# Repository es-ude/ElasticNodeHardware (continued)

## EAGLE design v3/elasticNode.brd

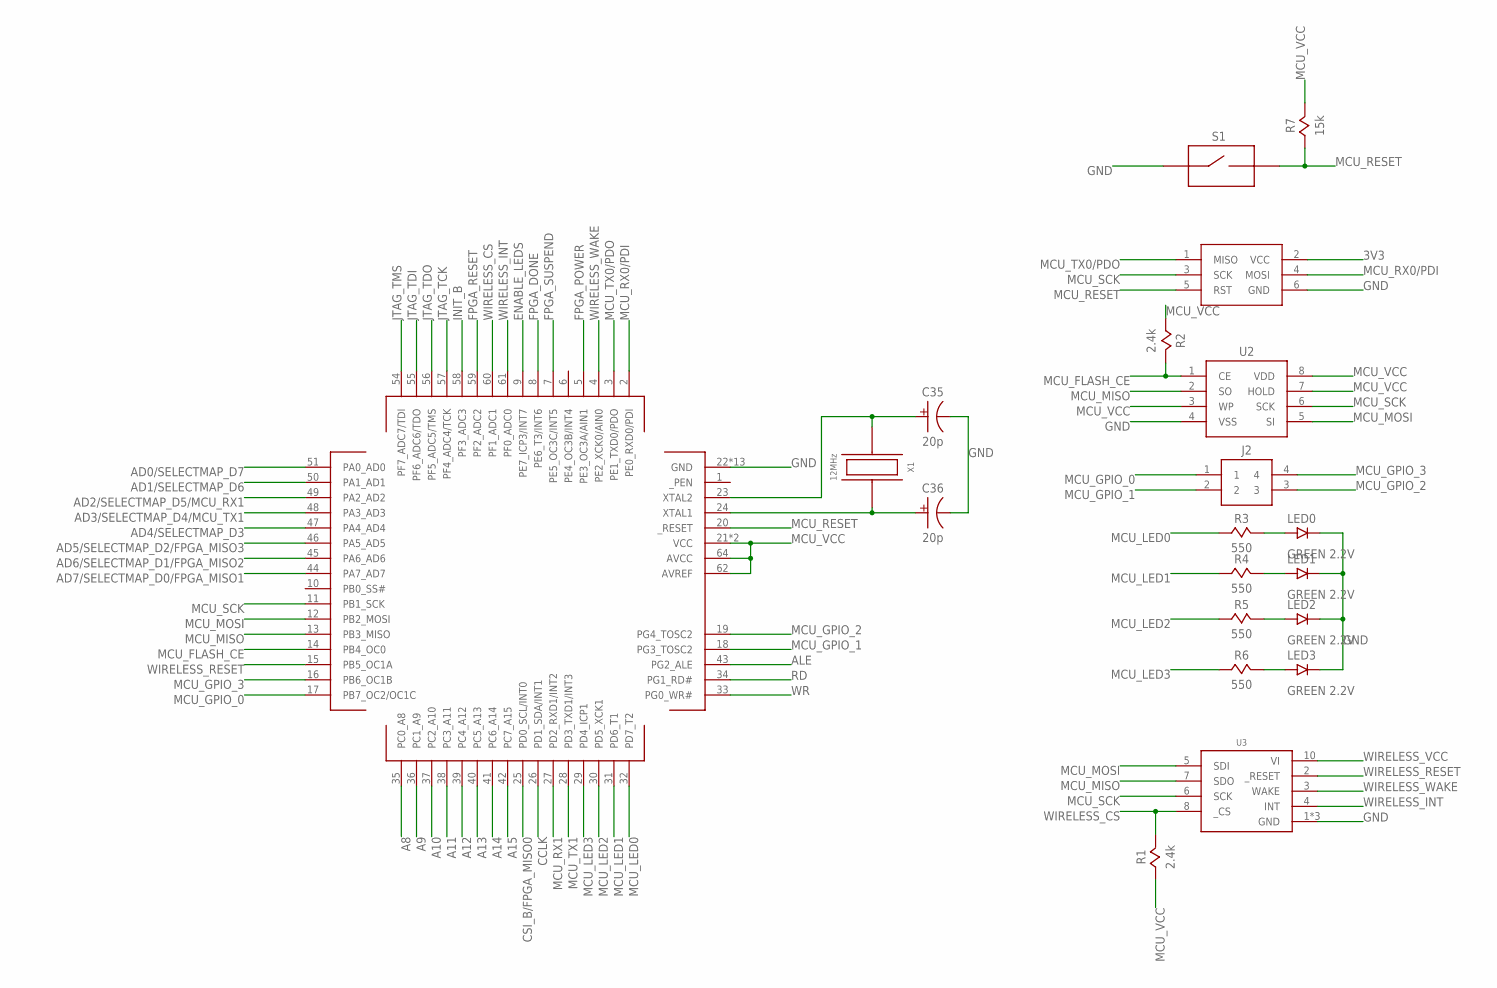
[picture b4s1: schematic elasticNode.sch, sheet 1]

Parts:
C35, C36: 20p; 0805
J1: ISP_CONN_6PIN; 3X2_HEADER_SMT
J2: FEMALE_HEADER_2X2; 2X2_HEADER
LED0, LED1, LED2, LED3: GREEN 2.2V; 0805
R1, R2: 2.4k; 0805
R3, R4, R5, R6: 550; 0805
R7: 15k; 0805
S1: SPST_BUTTON2PIN_SMT; SPST_2PIN_SMT
U1: ATMEGA64AQFN; QFN64
U2: SST26VF032B; SOIC8
U3: MRF24J40MA
X1: 12MHz; 3.2X2.5_OSC

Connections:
3V3: J1.2 (VCC); also elsewhere on the board
A8: U1.35 (PC0_A8); also elsewhere on the board
A9: U1.36 (PC1_A9); also elsewhere on the board
A10: U1.37 (PC2_A10); also elsewhere on the board
A11: U1.38 (PC3_A11); also elsewhere on the board
A12: U1.39 (PC4_A12); also elsewhere on the board
A13: U1.40 (PC5_A13); also elsewhere on the board
A14: U1.41 (PC6_A14); also elsewhere on the board
A15: U1.42 (PC7_A15); also elsewhere on the board
AD0/SELECTMAP_D7: U1.51 (PA0_AD0); also elsewhere on the board
AD1/SELECTMAP_D6: U1.50 (PA1_AD1); also elsewhere on the board
AD2/SELECTMAP_D5/MCU_RX1: U1.49 (PA2_AD2); also elsewhere on the board
AD3/SELECTMAP_D4/MCU_TX1: U1.48 (PA3_AD3); also elsewhere on the board
AD4/SELECTMAP_D3: U1.47 (PA4_AD4); also elsewhere on the board
AD5/SELECTMAP_D2/FPGA_MISO3: U1.46 (PA5_AD5); also elsewhere on the board
AD6/SELECTMAP_D1/FPGA_MISO2: U1.45 (PA6_AD6); also elsewhere on the board
AD7/SELECTMAP_D0/FPGA_MISO1: U1.44 (PA7_AD7); also elsewhere on the board
ALE: U1.43 (PG2_ALE); also elsewhere on the board
CCLK: U1.26 (PD1_SDA/INT1); also elsewhere on the board
CSI_B/FPGA_MISO0: U1.25 (PD0_SCL/INT0); also elsewhere on the board
ENABLE_LEDS: U1.9 (PE7_ICP3/INT7); also elsewhere on the board
FPGA_DONE: U1.8 (PE6_T3/INT6); also elsewhere on the board
FPGA_POWER: U1.5 (PE3_OC3A/AIN1); also elsewhere on the board
FPGA_RESET: U1.59 (PF2_ADC2); also elsewhere on the board
FPGA_SUSPEND: U1.7 (PE5_OC3C/INT5); also elsewhere on the board
GND: C35.2, C36.2, J1.6 (GND), LED0.2, LED1.2, LED2.2, LED3.2, S1.1, U1.22 (GND), U1.53 (GND), U1.63 (GND), U1.PAD (GND), U1.VIA1 (GND), U1.VIA2 (GND), U1.VIA3 (GND), U1.VIA4 (GND), U1.VIA5 (GND), U1.VIA6 (GND), U1.VIA7 (GND), U1.VIA8 (GND), U1.VIA9 (GND), U2.4 (VSS), U3.1 (GND), U3.11 (GND), U3.12 (GND); also elsewhere on the board
INIT_B: U1.58 (PF3_ADC3); also elsewhere on the board
JTAG_TCK: U1.57 (PF4_ADC4/TCK); also elsewhere on the board
JTAG_TDI: U1.55 (PF6_ADC6/TDO); also elsewhere on the board
JTAG_TDO: U1.56 (PF5_ADC5/TMS); also elsewhere on the board
JTAG_TMS: U1.54 (PF7_ADC7/TDI); also elsewhere on the board
MCU_FLASH_CE: R2.2, U1.14 (PB4_OC0), U2.1 (CE)
MCU_GPIO_0: J2.1, U1.17 (PB7_OC2/OC1C)
MCU_GPIO_1: J2.2, U1.18 (PG3_TOSC2)
MCU_GPIO_2: J2.3, U1.19 (PG4_TOSC2)
MCU_GPIO_3: J2.4, U1.16 (PB6_OC1B)
MCU_LED0: R3.1, U1.32 (PD7_T2)
MCU_LED1: R4.1, U1.31 (PD6_T1)
MCU_LED2: R5.1, U1.30 (PD5_XCK1)
MCU_LED3: R6.1, U1.29 (PD4_ICP1)
MCU_MISO: U1.13 (PB3_MISO), U2.2 (SO), U3.7 (SDO)
MCU_MOSI: U1.12 (PB2_MOSI), U2.5 (SI), U3.5 (SDI)
MCU_RESET: J1.5 (RST), R7.1, S1.2 (3), U1.20 (_RESET)
MCU_RX0/PDI: J1.4 (MOSI), U1.2 (PE0_RXD0/PDI)
MCU_RX1: U1.27 (PD2_RXD1/INT2); also elsewhere on the board
MCU_SCK: J1.3 (SCK), U1.11 (PB1_SCK), U2.6 (SCK), U3.6 (SCK)
MCU_TX0/PDO: J1.1 (MISO), U1.3 (PE1_TXD0/PDO)
MCU_TX1: U1.28 (PD3_TXD1/INT3); also elsewhere on the board
MCU_VCC: R1.1, R2.1, R7.2, U1.21 (VCC), U1.52 (VCC), U1.62 (AVREF), U1.64 (AVCC), U2.3 (WP), U2.7 (HOLD), U2.8 (VDD); also elsewhere on the board
unnamed: LED3.1, R6.2
unnamed: LED2.1, R5.2
unnamed: LED1.1, R4.2
unnamed: LED0.1, R3.2
RD: U1.34 (PG1_RD#); also elsewhere on the board
WIRELESS_CS: R1.2, U1.60 (PF1_ADC1), U3.8 (_CS)
WIRELESS_INT: U1.61 (PF0_ADC0), U3.4 (INT)
WIRELESS_RESET: U1.15 (PB5_OC1A), U3.2 (_RESET)
WIRELESS_VCC: U3.10 (VI); also elsewhere on the board
WIRELESS_WAKE: U1.4 (PE2_XCK0/AIN0), U3.3 (WAKE)
WR: U1.33 (PG0_WR#); also elsewhere on the board
XTAL1: C36.1, U1.24 (XTAL1), X1.1
XTAL2: C35.1, U1.23 (XTAL2), X1.3

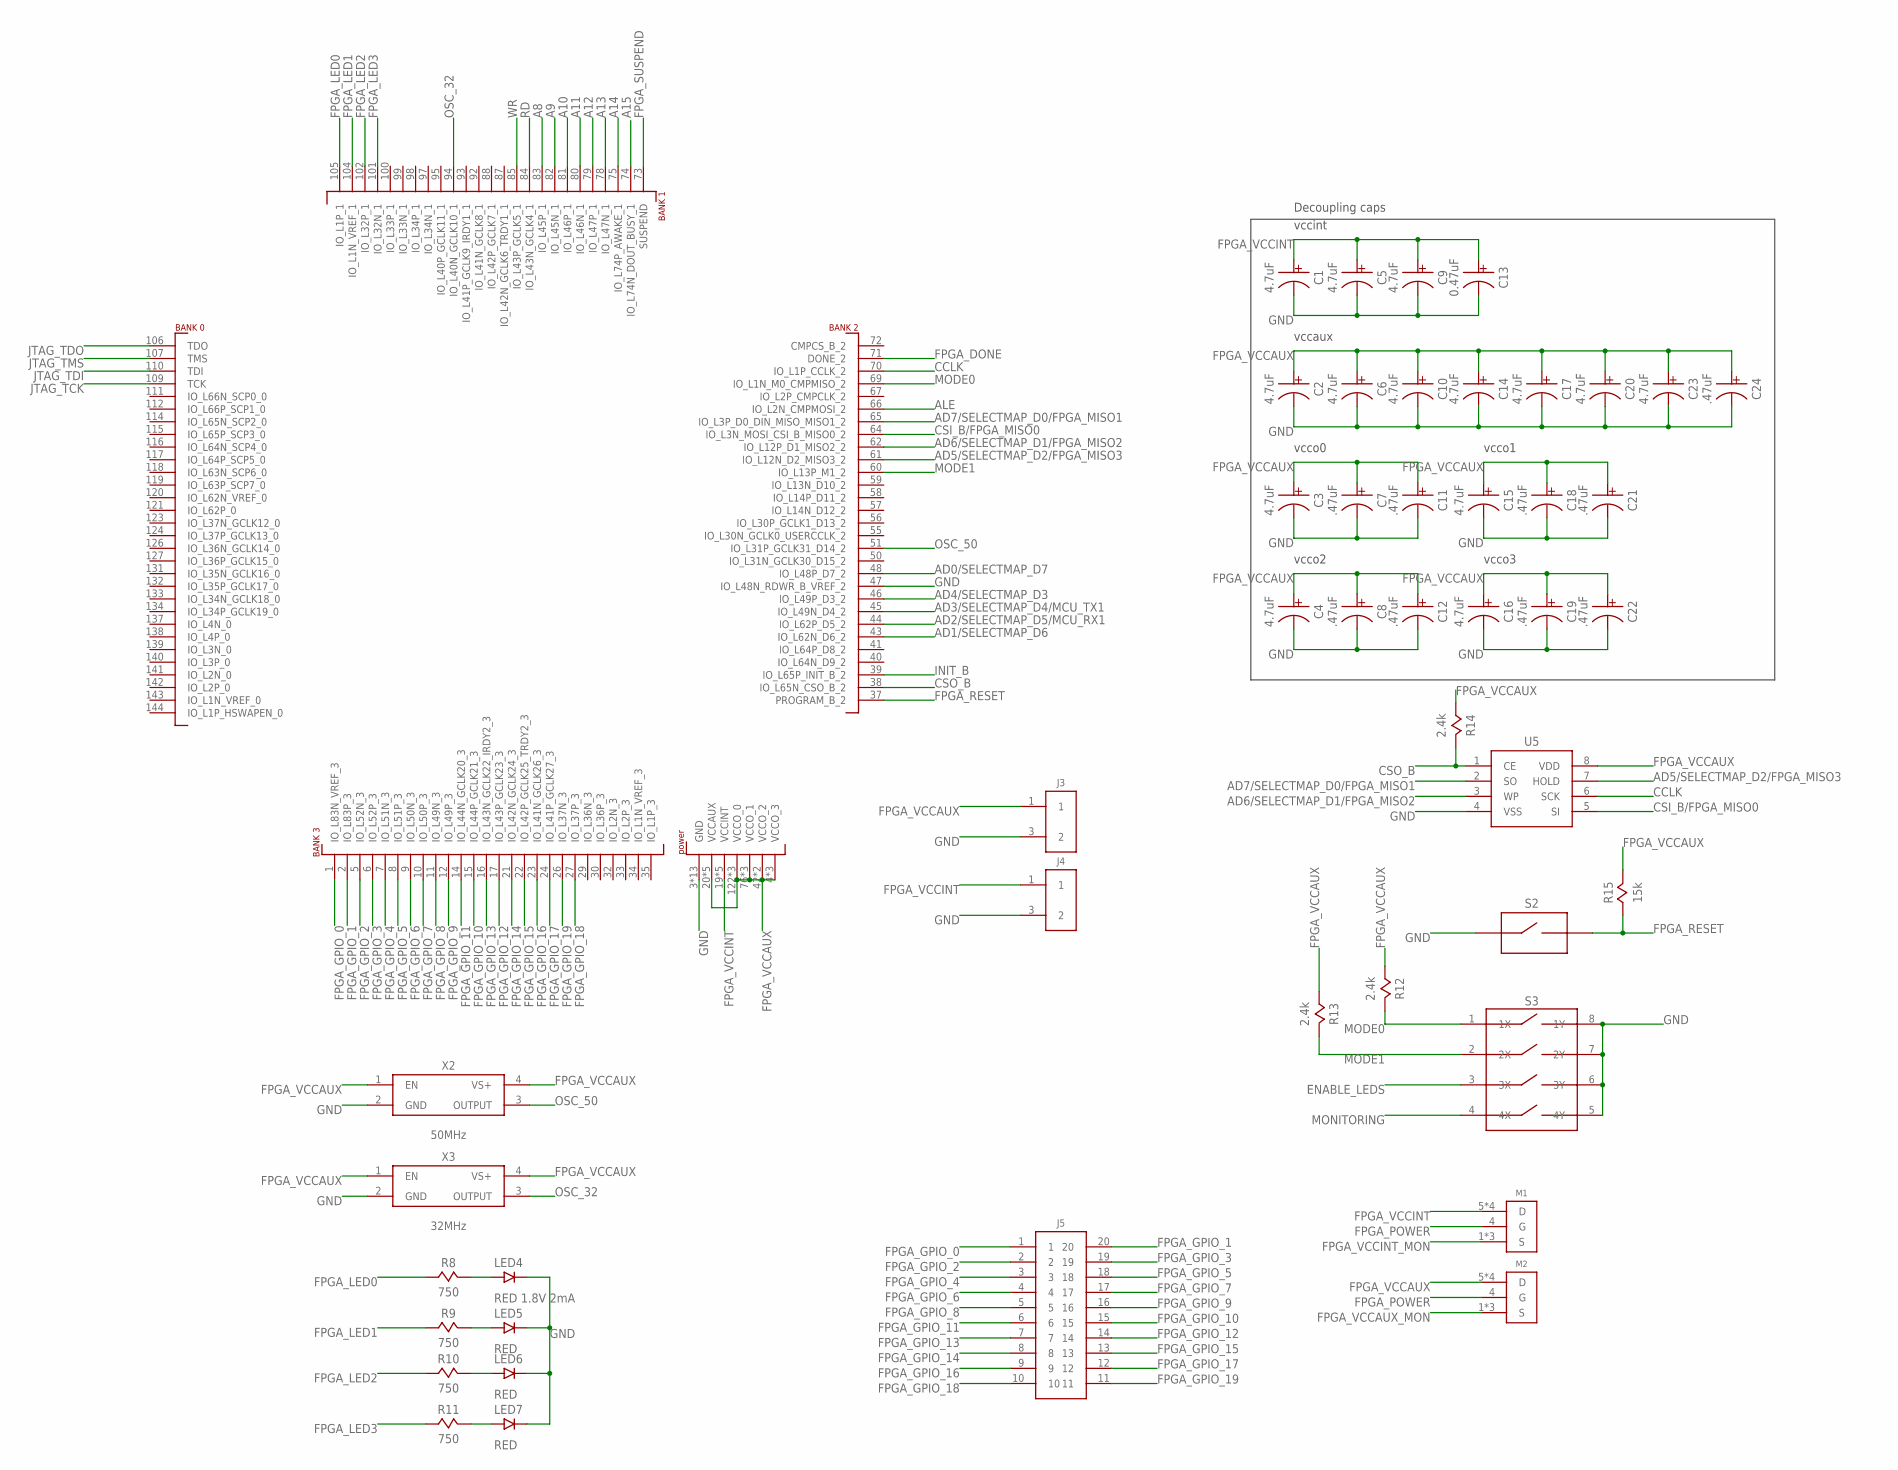
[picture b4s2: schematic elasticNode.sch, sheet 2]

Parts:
C1, C2, C3, C4, C5, C6, C9, C10, C14, C15, C16, C17, C20, C23: 4.7uF; 0805
C7, C8, C11, C12, C18, C19, C21, C22: .47uF; 0402
C13: 0.47uF; 0402
C24: .47uF; 0805
J3, J4: FEMALE_HEADER_2X1; 2X1_HEADER
J5: FEMALE_HEADER_10X2; 10X2_HEADER_SMT
LED4: RED 1.8V 2mA; 0805
LED5, LED6, LED7: RED; 0805
M1, M2: SISS23DN; POWERPAK1212-8
R8, R9, R10, R11: 750; 0805
R12, R13, R14: 2.4k; 0805
R15: 15k; 0805
S2: SPST_BUTTON2PIN_SMT; SPST_2PIN_SMT
S3: SPST_DIP_4; SPST_DIP4_SMT
U4: SPARTAN6-LX9; TQG144
U5: SST26VF032B; SOIC8
X2: 50MHz; 3.2X2.5_OSC
X3: 32MHz; 3.2X2.5_OSC

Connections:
A8: U4.83 (IO_L45P_1); also elsewhere on the board
A9: U4.82 (IO_L45N_1); also elsewhere on the board
A10: U4.81 (IO_L46P_1); also elsewhere on the board
A11: U4.80 (IO_L46N_1); also elsewhere on the board
A12: U4.79 (IO_L47P_1); also elsewhere on the board
A13: U4.78 (IO_L47N_1); also elsewhere on the board
A14: U4.75 (IO_L74P_AWAKE_1); also elsewhere on the board
A15: U4.74 (IO_L74N_DOUT_BUSY_1); also elsewhere on the board
AD0/SELECTMAP_D7: U4.48 (IO_L48P_D7_2); also elsewhere on the board
AD1/SELECTMAP_D6: U4.43 (IO_L62N_D6_2); also elsewhere on the board
AD2/SELECTMAP_D5/MCU_RX1: U4.44 (IO_L62P_D5_2); also elsewhere on the board
AD3/SELECTMAP_D4/MCU_TX1: U4.45 (IO_L49N_D4_2); also elsewhere on the board
AD4/SELECTMAP_D3: U4.46 (IO_L49P_D3_2); also elsewhere on the board
AD5/SELECTMAP_D2/FPGA_MISO3: U4.61 (IO_L12N_D2_MISO3_2), U5.7 (HOLD); also elsewhere on the board
AD6/SELECTMAP_D1/FPGA_MISO2: U4.62 (IO_L12P_D1_MISO2_2), U5.3 (WP); also elsewhere on the board
AD7/SELECTMAP_D0/FPGA_MISO1: U4.65 (IO_L3P_D0_DIN_MISO_MISO1_2), U5.2 (SO); also elsewhere on the board
ALE: U4.66 (IO_L2N_CMPMOSI_2); also elsewhere on the board
CCLK: U4.70 (IO_L1P_CCLK_2), U5.6 (SCK); also elsewhere on the board
CSI_B/FPGA_MISO0: U4.64 (IO_L3N_MOSI_CSI_B_MISO0_2), U5.5 (SI); also elsewhere on the board
CSO_B: R14.2, U4.38 (IO_L65N_CSO_B_2), U5.1 (CE)
ENABLE_LEDS: S3.3 (3X); also elsewhere on the board
FPGA_DONE: U4.71 (DONE_2); also elsewhere on the board
FPGA_GPIO_0: J5.1, U4.1 (IO_L83N_VREF_3)
FPGA_GPIO_1: J5.20, U4.2 (IO_L83P_3)
FPGA_GPIO_2: J5.2, U4.5 (IO_L52N_3)
FPGA_GPIO_3: J5.19, U4.6 (IO_L52P_3)
FPGA_GPIO_4: J5.3, U4.7 (IO_L51N_3)
FPGA_GPIO_5: J5.18, U4.8 (IO_L51P_3)
FPGA_GPIO_6: J5.4, U4.9 (IO_L50N_3)
FPGA_GPIO_7: J5.17, U4.10 (IO_L50P_3)
FPGA_GPIO_8: J5.5, U4.11 (IO_L49N_3)
FPGA_GPIO_9: J5.16, U4.12 (IO_L49P_3)
FPGA_GPIO_10: J5.15, U4.15 (IO_L44P_GCLK21_3)
FPGA_GPIO_11: J5.6, U4.14 (IO_L44N_GCLK20_3)
FPGA_GPIO_12: J5.14, U4.17 (IO_L43P_GCLK23_3)
FPGA_GPIO_13: J5.7, U4.16 (IO_L43N_GCLK22_IRDY2_3)
FPGA_GPIO_14: J5.8, U4.21 (IO_L42N_GCLK24_3)
FPGA_GPIO_15: J5.13, U4.22 (IO_L42P_GCLK25_TRDY2_3)
FPGA_GPIO_16: J5.9, U4.23 (IO_L41N_GCLK26_3)
FPGA_GPIO_17: J5.12, U4.24 (IO_L41P_GCLK27_3)
FPGA_GPIO_18: J5.10, U4.27 (IO_L37P_3)
FPGA_GPIO_19: J5.11, U4.26 (IO_L37N_3)
FPGA_LED0: R8.1, U4.105 (IO_L1P_1)
FPGA_LED1: R9.1, U4.104 (IO_L1N_VREF_1)
FPGA_LED2: R10.1, U4.102 (IO_L32P_1)
FPGA_LED3: R11.1, U4.101 (IO_L32N_1)
FPGA_POWER: M1.4 (G), M2.4 (G); also elsewhere on the board
FPGA_RESET: R15.1, S2.2 (3), U4.37 (PROGRAM_B_2); also elsewhere on the board
FPGA_SUSPEND: U4.73 (SUSPEND); also elsewhere on the board
FPGA_VCCAUX: C2.1, C3.1, C4.1, C6.1, C7.1, C8.1, C10.1, C11.1, C12.1, C14.1, C15.1, C16.1, C17.1, C18.1, C19.1, C20.1, C21.1, C22.1, C23.1, C24.1, J3.1, M2.5 (D), M2.6 (D), M2.7 (D), M2.8 (D), R12.1, R13.1, R14.1, R15.2, U4.4 (VCCO_3), U4.18 (VCCO_3), U4.20 (VCCAUX), U4.31 (VCCO_3), U4.36 (VCCAUX), U4.42 (VCCO_2), U4.53 (VCCAUX), U4.63 (VCCO_2), U4.76 (VCCO_1), U4.86 (VCCO_1), U4.90 (VCCAUX), U4.103 (VCCO_1), U4.122 (VCCO_0), U4.125 (VCCO_0), U4.129 (VCCAUX), U4.135 (VCCO_0), U5.8 (VDD), X2.1 (EN), X2.4 (VS+), X3.1 (EN), X3.4 (VS+)
FPGA_VCCAUX_MON: M2.1 (S), M2.2 (S), M2.3 (S); also elsewhere on the board
FPGA_VCCINT: C1.1, C5.1, C9.1, C13.1, J4.1, M1.5 (D), M1.6 (D), M1.7 (D), M1.8 (D), U4.19 (VCCINT), U4.28 (VCCINT), U4.52 (VCCINT), U4.89 (VCCINT), U4.128 (VCCINT)
FPGA_VCCINT_MON: M1.1 (S), M1.2 (S), M1.3 (S); also elsewhere on the board
GND: C1.2, C2.2, C3.2, C4.2, C5.2, C6.2, C7.2, C8.2, C9.2, C10.2, C11.2, C12.2, C13.2, C14.2, C15.2, C16.2, C17.2, C18.2, C19.2, C20.2, C21.2, C22.2, C23.2, C24.2, J3.3 (2), J4.3 (2), LED4.2, LED5.2, LED6.2, LED7.2, S2.1, S3.5 (4Y), S3.6 (3Y), S3.7 (2Y), S3.8 (1Y), U4.3 (GND), U4.13 (GND), U4.25 (GND), U4.47 (IO_L48N_RDWR_B_VREF_2), U4.49 (GND), U4.54 (GND), U4.68 (GND), U4.77 (GND), U4.91 (GND), U4.96 (GND), U4.108 (GND), U4.113 (GND), U4.130 (GND), U4.136 (GND), U5.4 (VSS), X2.2 (GND), X3.2 (GND); also elsewhere on the board
INIT_B: U4.39 (IO_L65P_INIT_B_2); also elsewhere on the board
JTAG_TCK: U4.109 (TCK); also elsewhere on the board
JTAG_TDI: U4.110 (TDI); also elsewhere on the board
JTAG_TDO: U4.106 (TDO); also elsewhere on the board
JTAG_TMS: U4.107 (TMS); also elsewhere on the board
MODE0: R12.2, S3.1 (1X), U4.69 (IO_L1N_M0_CMPMISO_2)
MODE1: R13.2, S3.2 (2X), U4.60 (IO_L13P_M1_2)
MONITORING: S3.4 (4X); also elsewhere on the board
unnamed: LED7.1, R11.2
unnamed: LED6.1, R10.2
unnamed: LED5.1, R9.2
unnamed: LED4.1, R8.2
OSC_32: U4.94 (IO_L40N_GCLK10_1), X3.3 (OUTPUT)
OSC_50: U4.51 (IO_L31P_GCLK31_D14_2), X2.3 (OUTPUT)
RD: U4.84 (IO_L43N_GCLK4_1); also elsewhere on the board
WR: U4.85 (IO_L43P_GCLK5_1); also elsewhere on the board

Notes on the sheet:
Decoupling caps
vccint
vccaux
vcco0
vcco1
vcco2
vcco3

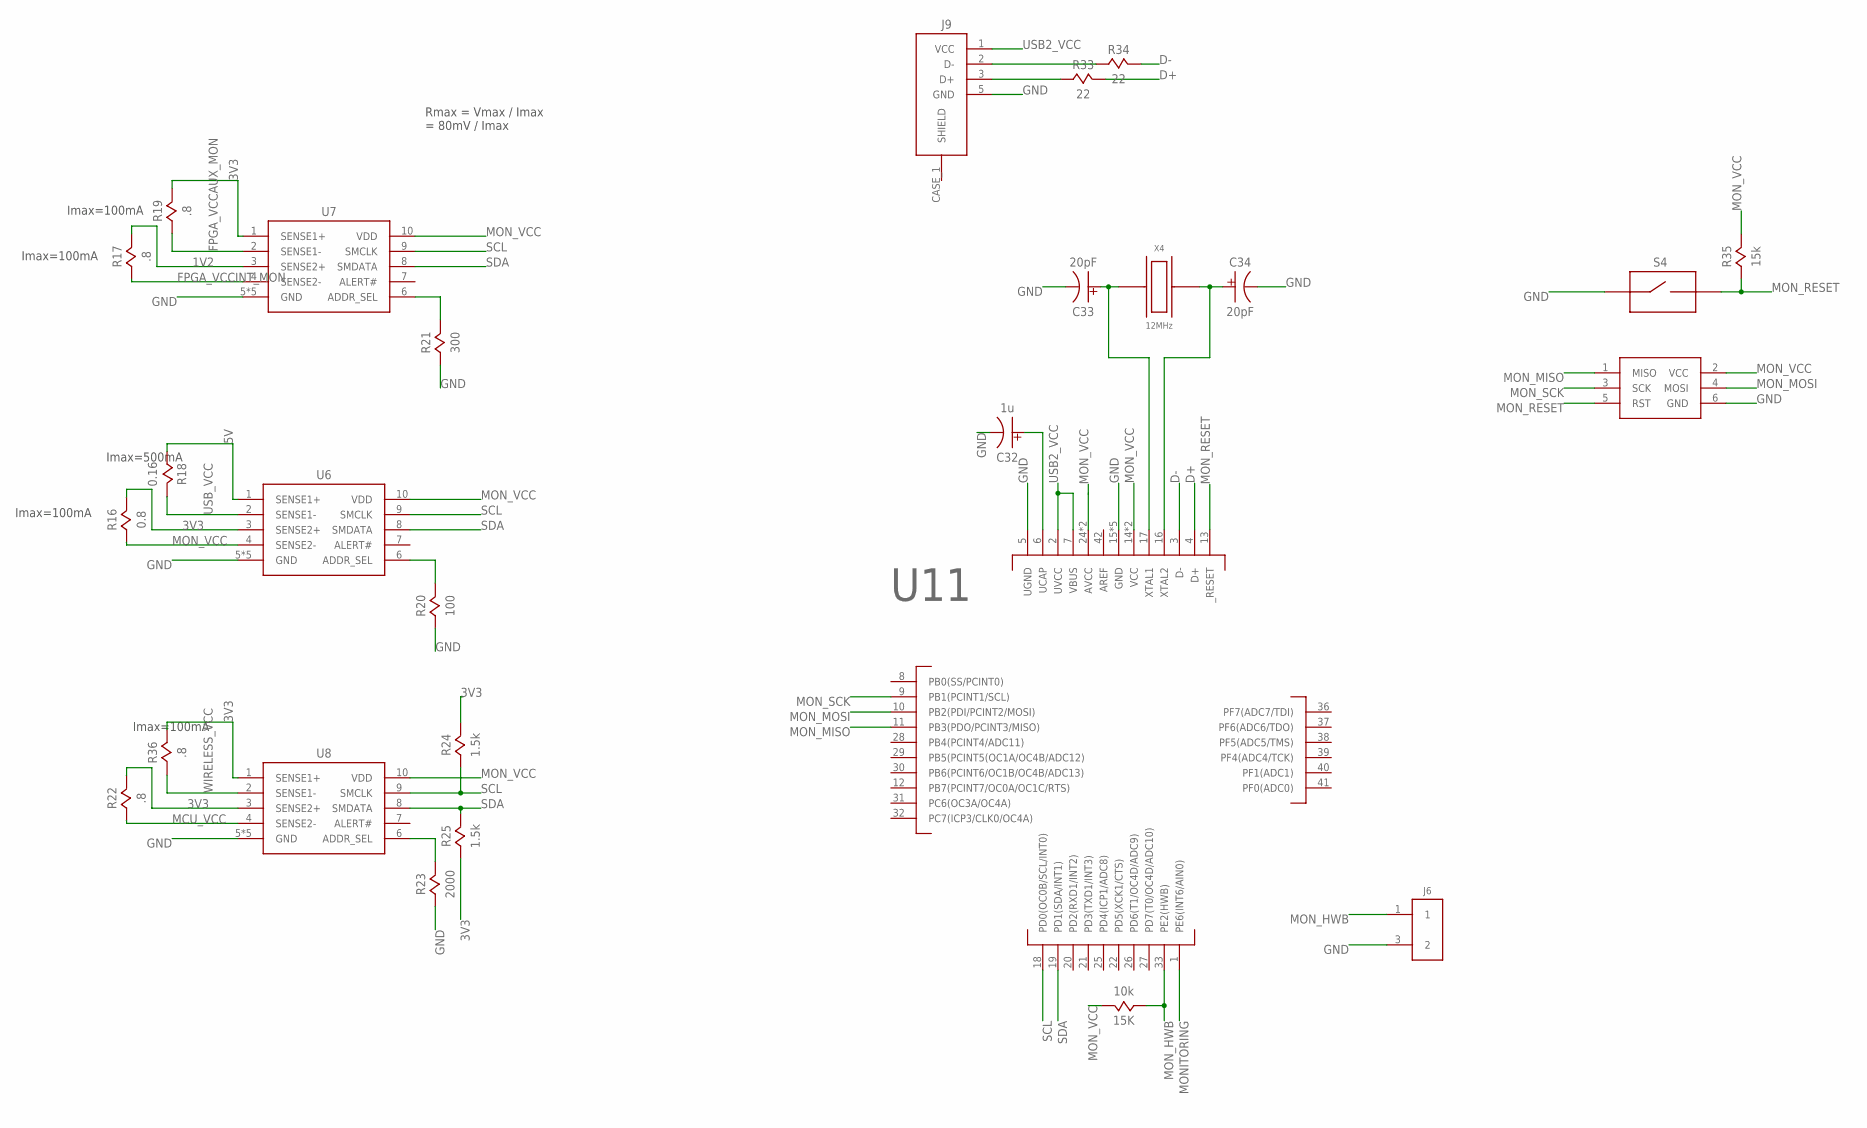
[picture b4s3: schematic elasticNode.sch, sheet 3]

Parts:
15K: 10k; 0805
C32: 1u; 0805
C33, C34: 20pF; 0805
J6: FEMALE_HEADER_2X1; 2X1_HEADER
J9: USB_CONNSMT; USB_MICRO_B_SMT
J10: ISP_CONN_6PIN; 3X2_HEADER_SMT
R16: 0.8; 0805
R17, R19, R22, R36: .8; 0805
R18: 0.16; 0805
R20: 100; 0805
R21: 300; 0805
R23: 2000; 0805
R24, R25: 1.5k; 0805
R33, R34: 22; 0805
R35: 15k; 0805
S4: SPST_BUTTON2PIN_SMT; SPST_2PIN_SMT
U6, U7, U8: PAC1720; VDFN10
U11: ATMEGA32U4; QFN44
X4: 12MHz; 3.2X2.5_OSC

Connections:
1V2: R17.2, U7.3 (SENSE2+); also elsewhere on the board
3V3: R16.2, R19.2, R22.2, R24.2, R25.1, R36.1, U6.3 (SENSE2+), U7.1 (SENSE1+), U8.1 (SENSE1+), U8.3 (SENSE2+); also elsewhere on the board
5V: R18.1, U6.1 (SENSE1+); also elsewhere on the board
D+: R33.2, U11.4 (D+)
D-: R34.2, U11.3 (D-)
FPGA_VCCAUX_MON: R19.1, U7.2 (SENSE1-); also elsewhere on the board
FPGA_VCCINT_MON: R17.1, U7.4 (SENSE2-); also elsewhere on the board
GND: C32.2, C33.2, C34.2, J6.3 (2), J9.5 (GND), J10.6 (GND), R20.1, R21.1, R23.1, S4.1, U6.5 (GND), U6.P$1 (GND), U6.P$2 (GND), U6.P$3 (GND), U6.P$4 (GND), U7.5 (GND), U7.P$1 (GND), U7.P$2 (GND), U7.P$3 (GND), U7.P$4 (GND), U8.5 (GND), U8.P$1 (GND), U8.P$2 (GND), U8.P$3 (GND), U8.P$4 (GND), U11.5 (UGND), U11.15 (GND), U11.23 (GND), U11.35 (GND), U11.43 (GND), U11.45 (GND); also elsewhere on the board
MCU_VCC: R22.1, U8.4 (SENSE2-); also elsewhere on the board
MONITORING: U11.1 (PE6(INT6/AIN0)); also elsewhere on the board
MON_HWB: 15K.1, J6.1, U11.33 (PE2(HWB))
MON_MISO: J10.1 (MISO), U11.11 (PB3(PDO/PCINT3/MISO))
MON_MOSI: J10.4 (MOSI), U11.10 (PB2(PDI/PCINT2/MOSI))
MON_RESET: J10.5 (RST), R35.1, S4.2 (3), U11.13 (_RESET)
MON_SCK: J10.3 (SCK), U11.9 (PB1(PCINT1/SCL))
MON_VCC: 15K.2, J10.2 (VCC), R16.1, R35.2, U6.4 (SENSE2-), U6.10 (VDD), U7.10 (VDD), U8.10 (VDD), U11.14 (VCC), U11.24 (AVCC), U11.34 (VCC), U11.44 (AVCC)
MON_XTAL1: C33.1, U11.17 (XTAL1), X4.1
MON_XTAL2: C34.1, U11.16 (XTAL2), X4.3
unnamed: R23.2, U8.6 (ADDR_SEL)
unnamed: R21.2, U7.6 (ADDR_SEL)
unnamed: R20.2, U6.6 (ADDR_SEL)
unnamed: J9.3 (D+), R33.1
unnamed: J9.2 (D-), R34.1
SCL: R24.1, U6.9 (SMCLK), U7.9 (SMCLK), U8.9 (SMCLK), U11.18 (PD0(OC0B/SCL/INT0))
SDA: R25.2, U6.8 (SMDATA), U7.8 (SMDATA), U8.8 (SMDATA), U11.19 (PD1(SDA/INT1))
UCAP: C32.1, U11.6 (UCAP)
USB2_VCC: J9.1 (VCC), U11.2 (UVCC), U11.7 (VBUS)
USB_VCC: R18.2, U6.2 (SENSE1-); also elsewhere on the board
WIRELESS_VCC: R36.2, U8.2 (SENSE1-); also elsewhere on the board

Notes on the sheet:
Rmax = Vmax / Imax = 80mV / Imax
Imax=100mA
Imax=500mA

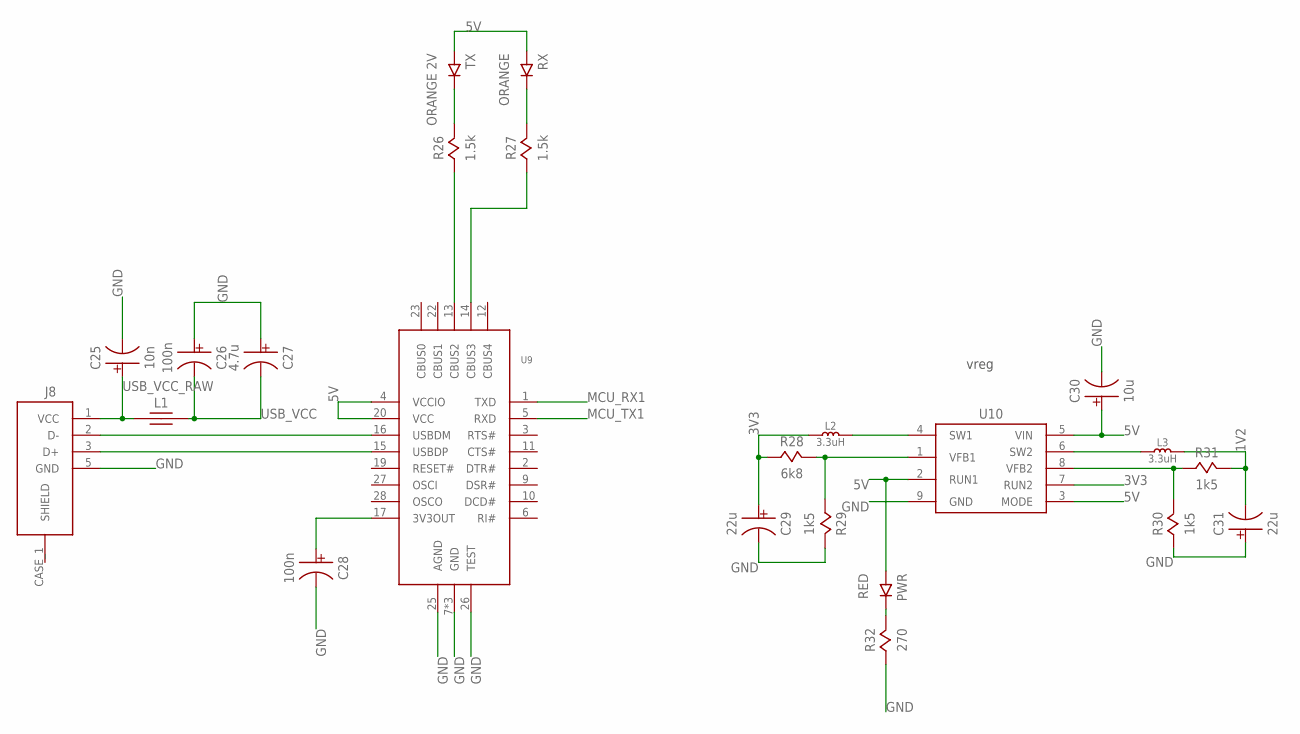
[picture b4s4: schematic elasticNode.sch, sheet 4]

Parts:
C25: 10n; 0805
C26, C28: 100n; 0805
C27: 4.7u; 0805
C29, C31: 22u; 0805
C30: 10u; 0805
J8: USB_CONNSMT; USB_MICRO_B_SMT
L1: 40Ohm 1.5A; 0805
L2, L3: 3.3uH; 0805
PWR: RED; 0805
R26, R27: 1.5k; 0805
R28: 6k8; 0805
R29, R30, R31: 1k5; 0805
R32: 270; 0805
RX: ORANGE; 0805
TX: ORANGE 2V; 0805
U9: FT232RSSOP28; SSOP28
U10: LTC3419DFN; DFN8

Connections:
1V2: C31.2, L3.2, R31.2; also elsewhere on the board
3V3: C29.1, L2.1, R28.1, U10.7 (RUN2); also elsewhere on the board
5V: C30.1, PWR.1, RX.1, TX.1, U9.4 (VCCIO), U9.20 (VCC), U10.2 (RUN1), U10.3 (MODE), U10.5 (VIN); also elsewhere on the board
FTDI_RXLED: R27.1, U9.14 (CBUS3)
GND: C25.2, C26.1, C27.1, C28.2, C29.2, C30.2, C31.1, J8.5 (GND), R29.2, R30.1, R32.1, U9.7 (GND), U9.18 (GND), U9.21 (GND), U9.25 (AGND), U9.26 (TEST), U10.9 (GND); also elsewhere on the board
MCU_RX1: U9.1 (TXD); also elsewhere on the board
MCU_TX1: U9.5 (RXD); also elsewhere on the board
unnamed: L2.2, U10.4 (SW1)
unnamed: R28.2, R29.1, U10.1 (VFB1)
unnamed: C28.1, U9.17 (3V3OUT)
unnamed: R30.2, R31.1, U10.8 (VFB2)
unnamed: L3.1, U10.6 (SW2)
unnamed: R26.1, U9.13 (CBUS2)
unnamed: R26.2, TX.2
unnamed: R27.2, RX.2
unnamed: PWR.2, R32.2
USBD+: J8.3 (D+), U9.15 (USBDP)
USBD-: J8.2 (D-), U9.16 (USBDM)
USB_VCC: C26.2, C27.2, L1.2; also elsewhere on the board
USB_VCC_RAW: C25.1, J8.1 (VCC), L1.1

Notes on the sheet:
vreg

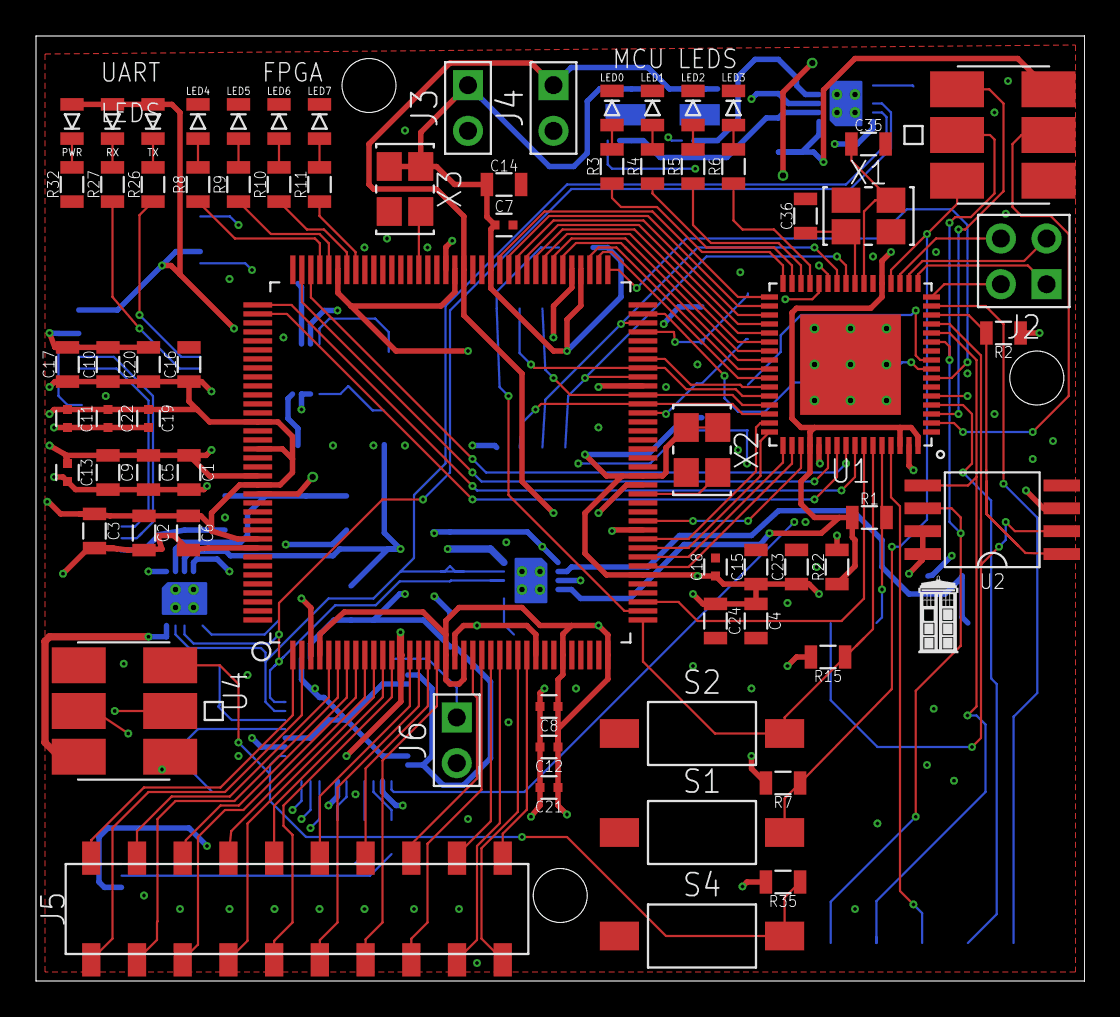
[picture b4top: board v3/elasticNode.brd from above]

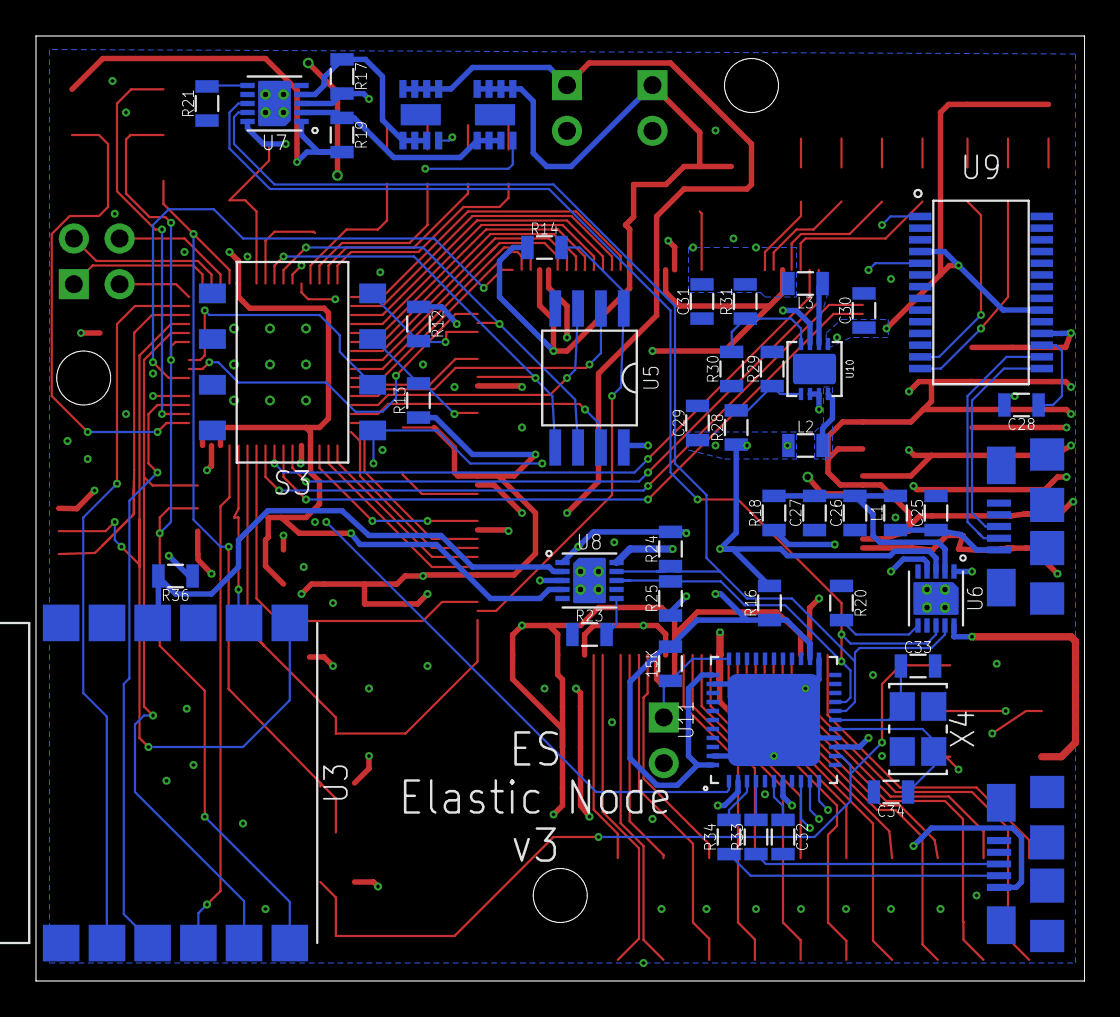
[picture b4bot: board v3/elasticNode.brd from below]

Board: 4 copper layers, 58.2 x 52.5 mm, 117 parts (47 on the bottom side), 135 nets.

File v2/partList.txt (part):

Partlist

Exported from elasticNode.brd at 07.08.17 2:13 PM

EAGLE Version 8.2.2 Copyright (c) 1988-2017 Autodesk, Inc.

Assembly variant: 

Part     Value               Package         Library    Position (mm)         Orientation

C1       4.7uF               0805            passive    (9.5 28.25)           R270
C2       4.7uF               0805            passive    (17.36 11.25)         R0
C3       4.7uF               0805            passive    (19.5 42.25)          R0
C4       4.7uF               0805            passive    (23.25 11)            R180
C5       4.7uF               0805            passive    (7.25 28.25)          R270
C6       4.7uF               0805            passive    (17.36 13.46)         R0
C7       .47uF               0402            passive    (19.5 44.5)           R0
C8       .47uF               0402            passive    (21.25 11.5)          R90
C9       4.7uF               0805            passive    (5 28.25)             R270
C10      4.7uF               0805            passive    (27.75 48)            R0
C11      .47uF               0402            passive    (19.5 46.75)          R0
C12      .47uF               0402            passive    (20.5 8.75)           R180
C13      0.47uF              0402            passive    (2.75 28.25)          R270
C14      4.7uF               0805            passive    (27.75 45.75)         R0
C15      4.7uF               0805            passive    (43.25 27.5)          R90
C16      4.7uF               0805            passive    (7.25 25)             R270
C17      4.7uF               0805            passive    (27.75 43.5)          R0
C18      .47uF               0402            passive    (41 27.5)             R90
C19      .47uF               0402            passive    (5 25)                R270
C20      4.7uF               0805            passive    (27.75 41.25)         R0
C21      .47uF               0402            passive    (38.75 27.5)          R90
C22      .47uF               0402            passive    (2.75 25)             R270
C23      4.7uF               0805            passive    (43.25 24.75)         R270
C24      .47uF               0805            passive    (41 24.75)            R270
C25      10n                 0805            passive    (78.75 21)            R180
C26      100n                0805            passive    (78.75 25.5)          R180
C27      4.7u                0805            passive    (78.75 27.75)         R180
C28      100n                0805            passive    (74.35 15.05)         R90
C29      22u                 0805            passive    (63.5 35.5)           R0
C30      10u                 0805            passive    (67.8 26.3)           R180
C31      22u                 0805            passive    (70.25 35.5)          R180
J1       ISP_CONN_6PIN       3X2_HEADER_SMT  connectors (57.5 17)             R90
J2       FEMALE_HEADER_2X2   2X2_HEADER      connectors (64.25 48.5)          R180
J3       FEMALE_HEADER_2X1   2X1_HEADER      connectors (16.25 49.75)         R180
J4       FEMALE_HEADER_2X1   2X1_HEADER      connectors (23 49.75)            R180
J5       FEMALE_HEADER_5X2   5X2_HEADER      connectors (4.5 36.75)           R270
J6       FEMALE_HEADER_5X2   5X2_HEADER      connectors (4.5 16.9)            R90
J7       JTAG_CONN_6PINTHT   6X1_HEADER      connectors (38.5 44.25)          R270
J8       USB_CONNSMT         USB_MICRO_B_SMT connectors (77 13.5)             R90
L1       40Ohm 1.5A          0805            passive    (78.75 23.25)         R180
L2       3.3uH               0805            passive    (62.25 29.75)         R270
L3       3.3uH               0805            passive    (71.25 29.75)         R90
LED0     GREEN 2.2V          0805            opto       (68 45.25)            R90
LED1     GREEN 2.2V          0805            opto       (70.25 45.25)         R90
LED2     GREEN 2.2V          0805            opto       (72.5 45.25)          R90
LED3     GREEN 2.2V          0805            opto       (74.75 45.25)         R90
LED4     RED 1.8V 2mA        0805            opto       (10 45)               R90
LED5     RED                 0805            opto       (12.25 45)            R90
LED6     RED                 0805            opto       (14.5 45)             R90
LED7     RED                 0805            opto       (16.75 45)            R90
PWR      RED                 0805            opto       (70.25 4.5)           R90
R1       2.4k                0805            passive    (54.6 35)             R135
R2       2.4k                0805            passive    (53.5 19.75)          MR315
R3       550                 0805            passive    (68 42.25)            R90
R4       550                 0805            passive    (70.25 42.25)         R90
R5       550                 0805            passive    (72.5 42.25)          R90
R6       550                 0805            passive    (74.75 42.25)         R90
R7       15k                 0805            passive    (52 18.75)            R90
R8       750                 0805            passive    (10 42.25)            R90
R9       750                 0805            passive    (12.25 42.25)         R90
R10      750                 0805            passive    (14.5 42.25)          R90
R11      750                 0805            passive    (16.75 42.25)         R90
R12      2.4k                0805            passive    (34.25 16.5)          R270
R13      2.4k                0805            passive    (36.5 16.5)           R270
R14      2.4k                0805            passive    (17.5 8.75)           R270
R15      15k                 0805            passive    (15.25 9.5)           R0
R16      0.8                 0805            passive    (73.75 36.5)          R270
R17      .8                  0805            passive    (30.5 48.75)          R0
R18      0.16                0805            passive    (78.75 30)            R180
R19      .8                  0805            passive    (30.5 51)             R0
R20      100                 0805            passive    (73.5 33.5)           R270
R21      300                 0805            passive    (30.75 42.25)         R0
R22      .8                  0805            passive    (47.5 18.75)          R270
R23      2000                0805            passive    (44.5 22)             R180
R24      1.5k                0805            passive    (48.5 10.5)           MR180
R25      1.5k                0805            passive    (54 14)               MR180
R26      1.5k                0805            passive    (65.75 8)             R270
R27      1.5k                0805            passive    (68 8)                R270
R28      6k8                 0805            passive    (63.25 33.1)          R0
R29      1k5                 0805            passive    (65.5 31.6)           R0
R30      1k5                 0805            passive    (67.5 33.1)           R0
R31      1k5                 0805            passive    (70.25 33.1)          R0
R32      270                 0805            passive    (70.25 8)             R270
RX       ORANGE              0805            opto       (68 4.5)              R90
S1       SPST_BUTTON2PIN_SMT SPST_2PIN_SMT   connectors (57.5 9.25)           R180
S2       SPST_BUTTON2PIN_SMT SPST_2PIN_SMT   connectors (21.75 4.5)           R180
S3       SPST_DIP_2SMT       SPST_DIP2_SMT   connectors (37.5 9.75)           R0
TX       ORANGE 2V           0805            opto       (65.75 4.5)           R90
U1       ATMEGA64AQFN        QFN64           ic         (47.06 26.59)         MR0
U2       SST26VF032B         SOIC8           ic         (57.78 22.15)         MR90
U3       MRF24J40MA          MRF24J40MA      wireless   (50.75 44.5)          R0
U4       SPARTAN6-LX9        TQG144          fpga       (23.56 28.48)         R0
U5       SST26VF032B         SOIC8           ic         (29.63 11.41)         R180
U6       PAC1720             VDFN10          sensors    (77 33.5)             R270
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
